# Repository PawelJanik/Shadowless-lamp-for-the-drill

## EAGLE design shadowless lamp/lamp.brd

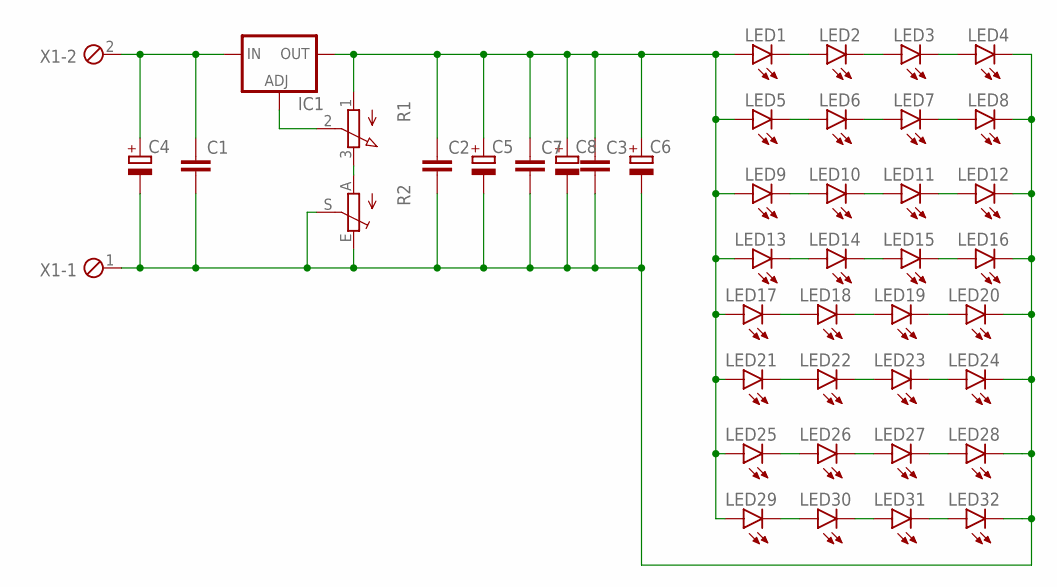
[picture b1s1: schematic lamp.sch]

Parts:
C1, C2, C3, C7: C-EU025-025X050; C025-025X050
C4, C5, C6, C8: CPOL-EUE2-5; E2-5
IC1: LM317TS; 317TS
LED1, LED2, LED3, LED4, LED5, LED6, LED7, LED8, LED9, LED10, LED11, LED12, LED13, LED14, LED15, LED16, LED17, LED18, LED19, LED20, LED21, LED22, LED23, LED24, LED25, LED26, LED27, LED28, LED29, LED30, LED31, LED32: LED3MM
R1: 3RP/1610N
R2: TRIM_EU-CA6V; CA6V
X1: MPT2; 2POL254

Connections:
GND: C1.2, C2.2, C3.2, C4.-, C5.-, C6.-, C7.2, C8.-, LED4.K (C), LED8.K (C), LED12.K (C), LED16.K (C), LED20.K (C), LED24.K (C), LED28.K (C), LED32.K (C), R2.E, R2.S, X1.1
unnamed: LED1.K (C), LED2.A
unnamed: LED2.K (C), LED3.A
unnamed: LED3.K (C), LED4.A
unnamed: LED5.K (C), LED6.A
unnamed: LED6.K (C), LED7.A
unnamed: LED7.K (C), LED8.A
unnamed: LED9.K (C), LED10.A
unnamed: LED10.K (C), LED11.A
unnamed: LED11.K (C), LED12.A
unnamed: LED15.K (C), LED16.A
unnamed: LED14.K (C), LED15.A
unnamed: LED13.K (C), LED14.A
unnamed: C1.1, C4.+, IC1.3 (IN), X1.2
unnamed: IC1.1 (ADJ), R1.2 (S)
unnamed: LED17.K (C), LED18.A
unnamed: R1.3 (E), R2.A
unnamed: LED18.K (C), LED19.A
unnamed: LED19.K (C), LED20.A
unnamed: LED21.K (C), LED22.A
unnamed: LED22.K (C), LED23.A
unnamed: LED23.K (C), LED24.A
unnamed: LED25.K (C), LED26.A
unnamed: LED26.K (C), LED27.A
unnamed: LED27.K (C), LED28.A
unnamed: LED31.K (C), LED32.A
unnamed: LED30.K (C), LED31.A
unnamed: LED29.K (C), LED30.A
V+: C2.1, C3.1, C5.+, C6.+, C7.1, C8.+, IC1.2 (OUT), LED1.A, LED5.A, LED9.A, LED13.A, LED17.A, LED21.A, LED25.A, LED29.A, R1.1 (A)

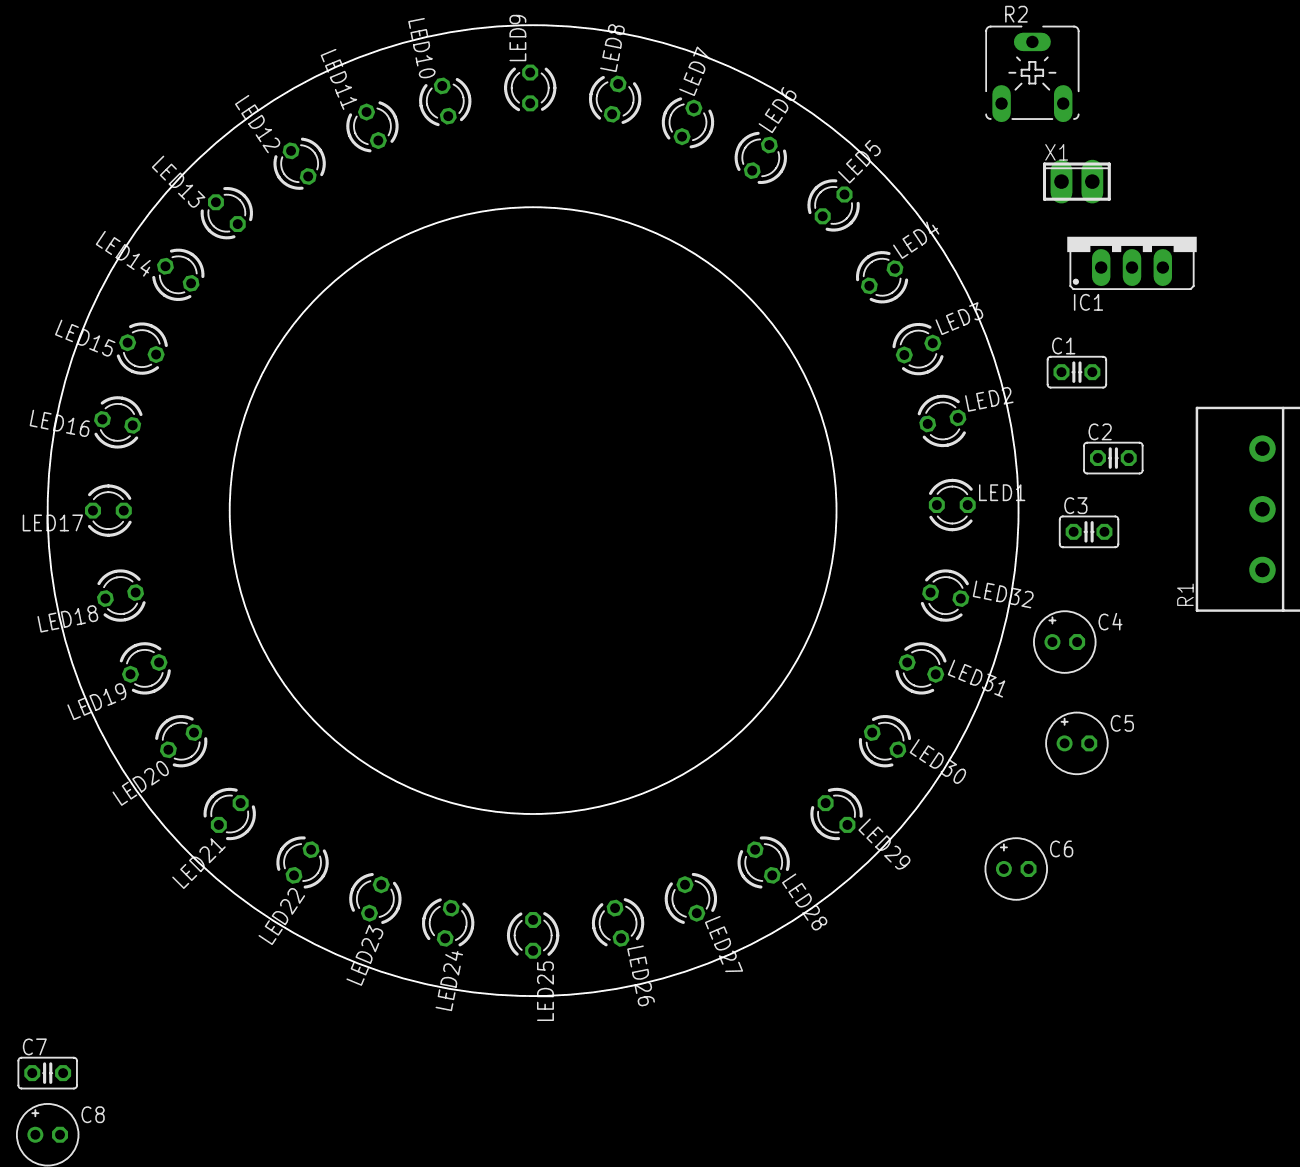
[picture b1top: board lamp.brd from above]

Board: 2 copper layers, 80.0 x 80.0 mm, 44 parts (0 on the bottom side), 29 nets.
